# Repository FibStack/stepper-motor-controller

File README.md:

# Stepper Motor Controller

## Overview

This repository includes the source files for the Stepper Motor Control board, capable of controlling the direction, steps, and speed of up to four stepper motors concurrently through the I2C interface. 

Kindly note that the project is currently in the prototype phase, and further changes and updates are expected.

## Project organization

- **hardware/** - this folder contains the board circuit schematic and PCB design files.
- **software/util** - contains the source code of a simple CLI application to interact with the board.
- **software/stepper-motor-controller** - contains the firmware source code for ATTiny devices.

## Development tools
- **[Microchip Studio 7.0](https://www.microchip.com/en-us/tools-resources/develop/microchip-studio)**: The IDE for writing and building source code for the ATTiny chip. We also use this tool to flash the chip.
- **[ATMEL-ICE](https://www.microchip.com/en-us/development-tool/ATATMEL-ICE)**: Hardware tool for flashing program and EEPROM memories.
- **GCC** compiler: To complie C utility code on Raspberry Pi.
- **[KiCad EDA](https://www.kicad.org/)**: Schematic and PCB design.

To construct the PCB, please export the gerber files according to the manufacturer's guidelines.

To build the CLI utility, navigate to the `util` folder and execute the `make` command. Please note that this works only on **Raspberry Pi OS**.

To build the ATTiny826 firmware, open the project in Microchip Studio. Build the solution to generate the `*.HEX` and `*.EEP` files. Next, use the appropriate tool available to flash the chip.

## BOM

| # | Components | Recommended models | Footprint | Quantity |
| --- | --- | --- | --- | --- |
| 1 | PCB | Recommended two-layer PCB board of 1.6 mm thickness | | 1 |
| 2 | U1 | SN74LS148 | SOIC-16, 3.9x9.9mm, pitch: 1.27mm | 1 |
| 3 | U2 | ATtiny826 | SOIC-20, 7.5x12.8mm, pitch: 1.27mm | 1 |
| 4 | C1, C4 | Any 1uF 50V SMD capacitor | 0603 (1608 metric) | 2 |
| 5 | C2 | Any 10nF 50V SMD capacitor | 0603 (1608 metric) | 1 |
| 6 | C3, C5 | Any 100nF 50V SMD capacitor | 0603 (1608 metric) | 2 |
| 7 | R1 | Any 470 - 1K 5% 1/4W SMD Resistor | 0603 (1608 metric) | 1 |
| 8 | R2-R13 | Any 10K 5% 1/4W SMD Resistor | 0603 (1608 metric) | 12 |
| 9 | Q1, Q2 | 2N7002 N-channel MOSFET transistor, 60V 300mA | SOT-23-2 | 2 |
| 10 | D1 | SMD LED RED | 0603 (1608 metric) | 1 |
| 11 | J1 | Extended GPIO Male Female Header, 2x20, pitch 2.54mm | 2x20 - P2.54mm | 1 |
| 12 | J2 | Optional, Male Header Connector, 2x3, pitch 2.54mm | 2x3 - P2.54mm | 1 |
| 13 | J3 | Any male connector, 1x2, pitch 2.54mm | 1x2 - P2.54mm | 1 |
| 14 | J4 | Male Header Connector, 2x8, pitch 2.54mm | 2x8 - P2.54mm | 1 |
| 15 | J5, J6, J7, J8 | Male Header Connector, 1x4, pitch 2.54mm | 1x4 - P2.54mm | 4 |
| 16 | SW1 | SPDT 3-pin vertical slide switch | P2.54mm | 1 |

## Documentation

For more detailed information about the board and the I2C protocol, please visit the [project page](https://fibstack.com/projects/stepper-motor-controller/).

## License Information
This product is open source!

Please review the LICENSE.md file for license information. Distributed as-is; no warranty is given.

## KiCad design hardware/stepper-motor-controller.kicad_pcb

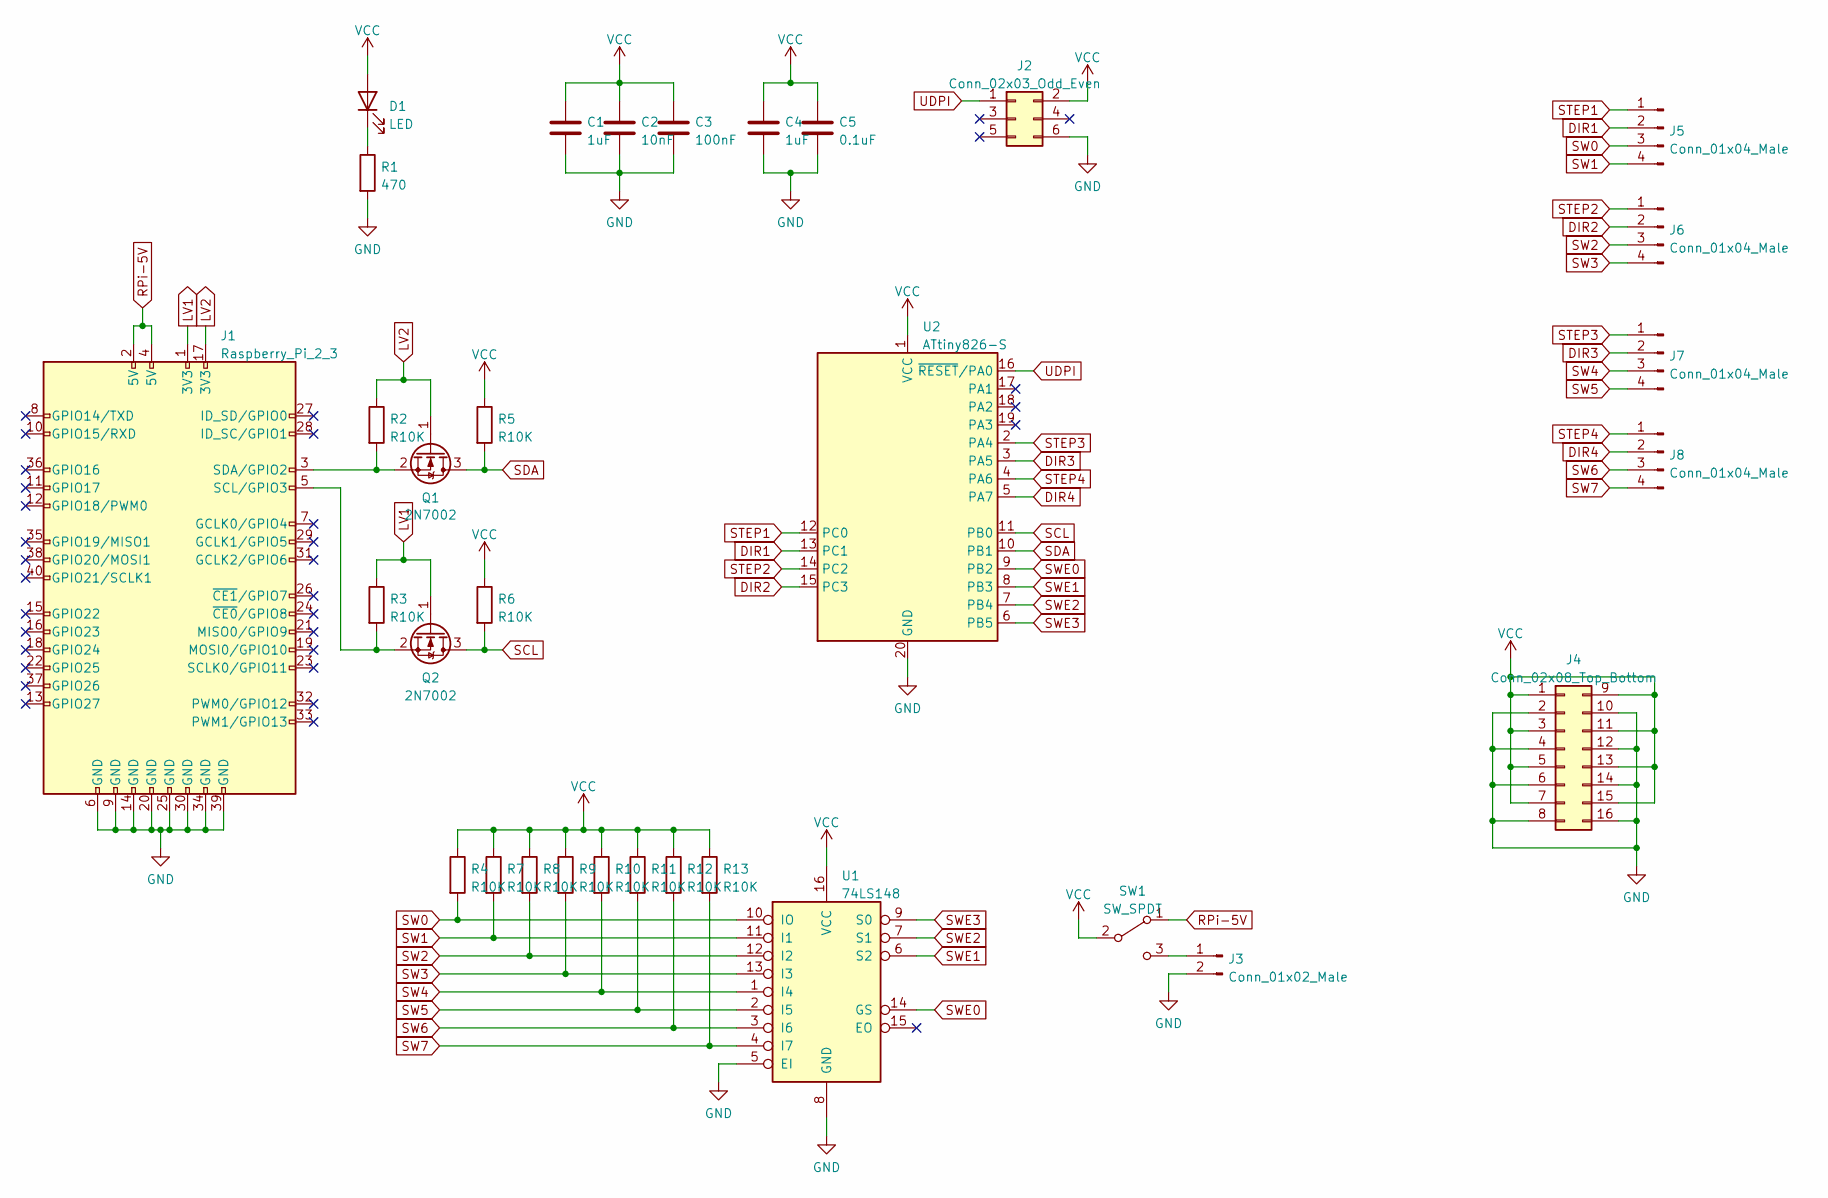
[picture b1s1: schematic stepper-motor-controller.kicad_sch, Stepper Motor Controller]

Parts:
C1, C4: 1uF; C_0603_1608Metric
C2: 10nF; C_0603_1608Metric
C3: 100nF; C_0603_1608Metric
C5: 0.1uF; C_0603_1608Metric
D1: LED; LED_0603_1608Metric
J1: Raspberry_Pi_2_3; PinHeader_2x20_P2.54mm_Vertical
J2: Conn_02x03_Odd_Even; PinHeader_2x03_P2.54mm_Vertical
J3: Conn_01x02_Male; PinHeader_1x02_P2.54mm_Vertical
J4: Conn_02x08_Top_Bottom; PinHeader_2x08_P2.54mm_Vertical
J5, J6, J7, J8: Conn_01x04_Male; PinHeader_1x04_P2.54mm_Vertical
Q1, Q2: 2N7002; SOT-23
R1: 470; R_0603_1608Metric
R2, R3, R4, R5, R6, R7, R8, R9, R10, R11, R12, R13: R10K; R_0603_1608Metric
SW1: SW_SPDT; PinHeader_1x03_P2.54mm_Vertical
U1: 74LS148; SOIC-16_3.9x9.9mm_P1.27mm
U2: ATtiny826-S; SOIC-20W_7.5x12.8mm_P1.27mm

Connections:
DIR1: J5.2, U2.13 (PC1)
DIR2: J6.2, U2.15 (PC3)
DIR3: J7.2, U2.3 (PA5)
DIR4: J8.2, U2.5 (PA7)
GND: C1.2, C2.2, C3.2, C4.2, C5.2, J1.6 (GND), J1.9 (GND), J1.14 (GND), J1.20 (GND), J1.25 (GND), J1.30 (GND), J1.34 (GND), J1.39 (GND), J2.6, J3.2, J4.2, J4.4, J4.6, J4.8, J4.10, J4.12, J4.14, J4.16, R1.2, U1.5 (EI), U1.8 (GND), U2.20 (GND)
LV1: J1.1 (3V3), Q2.1 (G), R3.1
LV2: J1.17 (3V3), Q1.1 (G), R2.1
unnamed: D1.1 (K), R1.1
unnamed: J1.3 (SDA/GPIO2), Q1.2 (S), R2.2
unnamed: J1.5 (SCL/GPIO3), Q2.2 (S), R3.2
unnamed: J3.1, SW1.3 (C)
RPi-5V: J1.2 (5V), J1.4 (5V), SW1.1 (A)
SCL: Q2.3 (D), R6.2, U2.11 (PB0)
SDA: Q1.3 (D), R5.2, U2.10 (PB1)
STEP1: J5.1, U2.12 (PC0)
STEP2: J6.1, U2.14 (PC2)
STEP3: J7.1, U2.2 (PA4)
STEP4: J8.1, U2.4 (PA6)
SW0: J5.3, R4.2, U1.10 (IO)
SW1: J5.4, R7.2, U1.11 (I1)
SW2: J6.3, R8.2, U1.12 (I2)
SW3: J6.4, R9.2, U1.13 (I3)
SW4: J7.3, R10.2, U1.1 (I4)
SW5: J7.4, R11.2, U1.2 (I5)
SW6: J8.3, R12.2, U1.3 (I6)
SW7: J8.4, R13.2, U1.4 (I7)
SWE0: U1.14 (GS), U2.9 (PB2)
SWE1: U1.6 (S2), U2.8 (PB3)
SWE2: U1.7 (S1), U2.7 (PB4)
SWE3: U1.9 (S0), U2.6 (PB5)
UDPI: J2.1, U2.16 (~RESET/PA0)
VCC: C1.1, C2.1, C3.1, C4.1, C5.1, D1.2 (A), J2.2, J4.1, J4.3, J4.5, J4.7, J4.9, J4.11, J4.13, J4.15, R4.1, R5.1, R6.1, R7.1, R8.1, R9.1, R10.1, R11.1, R12.1, R13.1, SW1.2 (B), U1.16 (VCC), U2.1 (VCC)

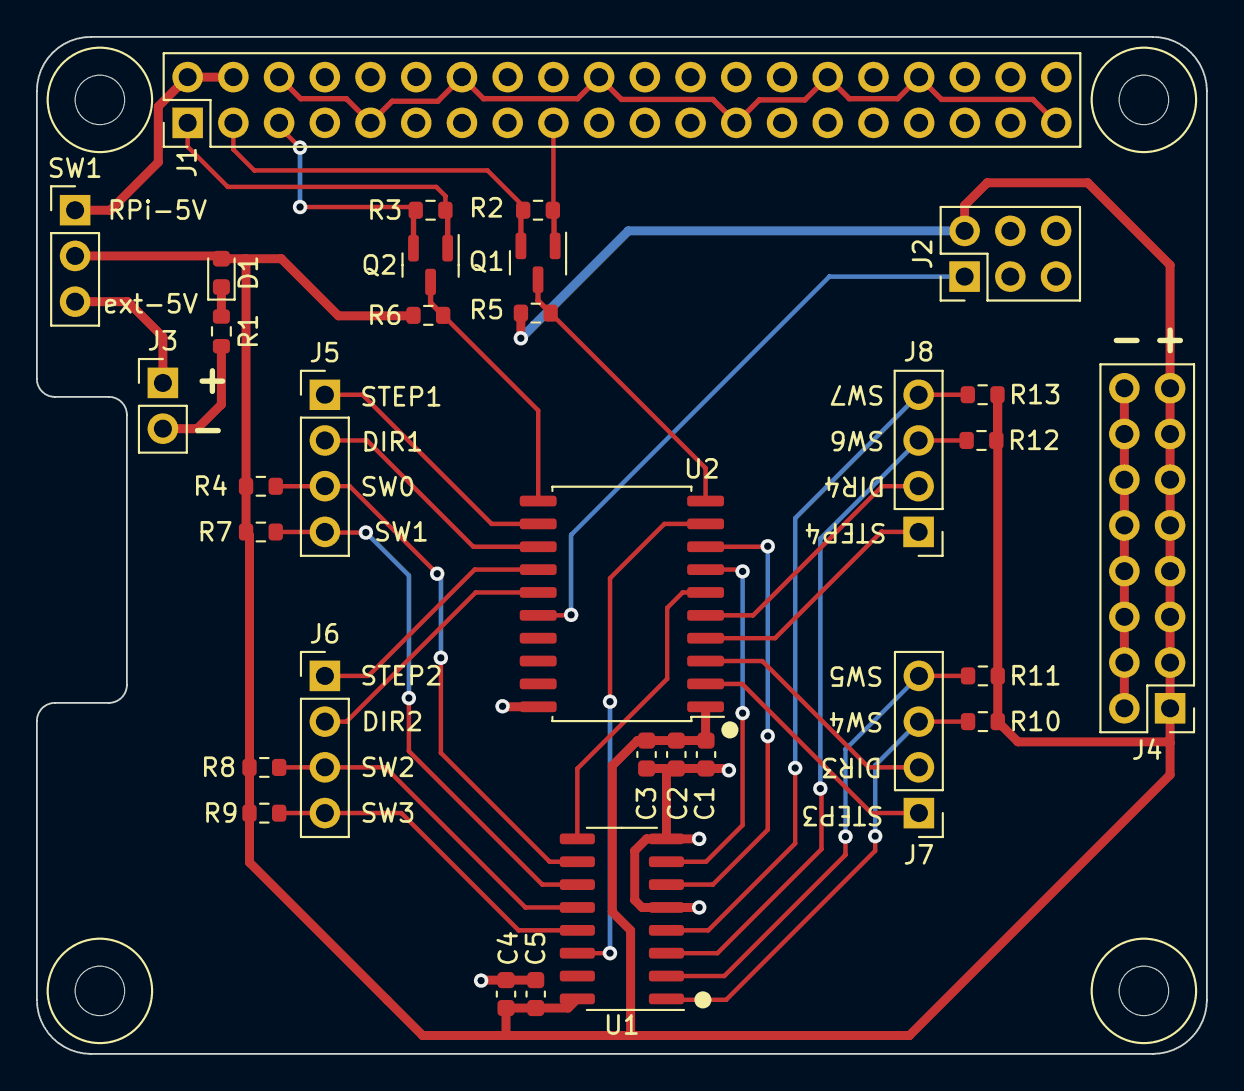
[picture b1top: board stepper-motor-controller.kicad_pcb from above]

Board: 2 copper layers, 65.0 x 56.5 mm, 32 parts (0 on the bottom side), 32 nets.

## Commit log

2023-06-14 Initial project files
2023-06-18 Added the project link. Fixed component name

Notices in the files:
hardware/stepper-motor-controller.kicad_pcb:
of the CERN-OHL-P V2 license (https:/cern.ch/cern-ohl).
Copyright © 2021-2023, FibStack
